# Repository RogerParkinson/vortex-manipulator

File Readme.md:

Vortex Manipulator
=

Mostly inspired by the wrist device worn by Captain Jack Harkness in _Dr Who_ and _Torchwood_, hence the name. However the design wandered somewhat from that initial idea so the look is a bit different. This is the idea I started with:

Mine is a little different, I needed more space to do what I want, so it is a bit fatter and it doesn't actually manipulate a time vortex (whatever that is). Instead it has the following functions:

 * Touch screen interface
 * Clock with optional beep and LED flash once a second, plus a function to set the time. It doesn't adjust automatically for daylight savings etc, but there is a UI to set the time manually.
 * Compass
 * Graphics demo
 * Dalek detector
 * Picture gallery (displays pictures from the SD card)
 * Heart rate monitor, including display graph and data log to SD card.
 * Sleep (power save) function, wakes up when the power button is pressed.
 * Notifications board. Messages from a Bluetooth device (eg a phone) display here.

[Lots more details here](https://github.com/RogerParkinson/vortex-manipulator)

Hardware consists of a Teensy 3.2 mounted on a custom board [the Main Board](eagle/MainBoard/Readme.md) which contains circuitry for charging the attached LiPo battery when the USB port is connected, and an LSM303 to provide compass and accelerometer functions.

A second [ILI9341 custom connector board](eagle/ILI9341-Touch-connector/Readme.md) connects to an ILI9341 touch screen. This board has a touch controller and a connector strip that matches the strip on the side of the main board.

There are some configuration settings stored on the SD card (file is hconfig.txt) which consists of the time zone, low pulse and high pulse rates. The pulse rates are used by the HRM to sound alarms if the pulse is outside that range. The time zone is used for the clock (except it isn't actually used now). The other files on the SD card are bmp files used for the picture gallery. These must be 240x320 images. All of these files are in the SDBackup directory.

Perhaps more importantly it is a development _platform_. There is plenty of spare capacity in the Teensy and there is still plenty of room in the assembly to add more stuff. The Main Board has connectors to unused pins on the Teensy as well. An example of adding more stuff is the heart rate monitor. I got hold of a better one which uses an I2C interface and, hardware-wise, it was simple to add the extra connections to the SDA and SCL for it, then a bit more programming and the job was done.

The assembly is a mix of leather and a 3D printed frame.

Parts
-

 * [Teensy 3.2](https://www.pjrc.com/store/teensy32.html) microprocessor board
 * [LSM303](http://nz.element14.com/stmicroelectronics/lsm303dlhc/sensor-3-ch-accel-mag-mod-14lga/dp/2068595) Compass/accelerometer IC *
 * [SD Card Reader](https://www.aliexpress.com/item/Free-Shipping-5PCS-67840-8001-Conn-SD-Card-HDR-9-POS-Solder-RA-SMD-Embossed-T/32651979617.html?spm=2114.01010208.3.8.SHXu2I&ws_ab_test=searchweb0_0,searchweb201602_3_10152_10065_10151_10068_436_10136_10157_10137_10060_10138_10155_10062_10156_10154_10056_10055_10054_10059_100032_100033_100031_10099_10103_10102_10096_10147_10052_10053_10050_10107_10142_10051_10084_10083_10080_10082_10081_10110_10175_10111_10112_10113_10114_10181_10037_10183_10182_10185_10033_10032_10078_10079_10077_10073_10070_10123,searchweb201603_2,ppcSwitch_4&btsid=7b9c1a86-e8c1-4082-b529-14cabbf02189&algo_expid=712bfc6c-3058-4115-9f9d-6d221787d2ec-1&algo_pvid=712bfc6c-3058-4115-9f9d-6d221787d2ec) *
 * [Lipo Battery 3.7v](https://www.aliexpress.com/item/3-7V-1000mah-753050-Lithium-Polymer-LiPo-Rechargeable-Battery-For-Mp3-MP4-MP5-DVD-PAD-mobile/32293277274.html?spm=2114.01010208.3.15.W3GGuF&ws_ab_test=searchweb0_0,searchweb201602_3_10152_10065_10151_10068_436_10136_10157_10137_10060_10138_10155_10062_10156_10154_10056_10055_10054_10059_100032_100033_100031_10099_10103_10102_10096_10147_10052_10053_10050_10107_10142_10051_10084_10083_10080_10082_10081_10110_10175_10111_10112_10113_10114_10181_10037_10183_10182_10185_10032_10078_10079_10077_10073_10070_10123,searchweb201603_2,ppcSwitch_4&btsid=7691371f-396d-424d-b6fc-32f0ece90527&algo_expid=46b76ba9-9c3b-4e16-846a-75c4c1e89c21-4&algo_pvid=46b76ba9-9c3b-4e16-846a-75c4c1e89c21)
 * [2.4" 240x320 SPI Serial TFT Color LCD Display Module+ILI9341 Touch Panel Screen](https://www.aliexpress.com/item/2-8-2-8-Inch-240x320-SPI-Serial-TFT-Color-LCD-Display-Module-Touch-Panel-Screen/32681743271.html?spm=2114.13010308.0.0.0kiaBY) Make sure you get a *touch* screen, there are screens in the same format/packing that just display with no touch.
 * [XPT2046 Touch Controller](https://www.aliexpress.com/item/Free-shipping-20pcs-lot-XPT2046-2046-TSSOP16-new-original/32639677099.html?spm=2114.13010608.0.0.BkDnSR) *
 * [MCP73811](https://www.aliexpress.com/item/100-new-origina-MCP73811T-420I-OT-battery-management-chip-73811-MCP73811-Free-shipping-best-match/32713220952.html?spm=2114.search0104.3.1.75a67645xuhfYb&ws_ab_test=searchweb0_0,searchweb201602_3_10065_10068_10547_319_317_10548_10696_10084_453_10924_10083_454_10925_10926_10618_10920_10921_10307_10922_537_536_5733313_5733211_10059_10884_5733113_10887_100031_321_5733413_322_10103_5733612_5733513,searchweb201603_2,ppcSwitch_0&algo_expid=36e5927f-8c98-4996-90c5-7ffab6aace2d-0&algo_pvid=36e5927f-8c98-4996-90c5-7ffab6aace2d) battery management chip *
 * [LP298X](http://www.datasheetcafe.com/lp298xs-datasheet-low-dropout-regulator/) voltage regulator *
 * [Speaker 8 ohm](https://www.aliexpress.com/item/Manufacturers-direct-sales-round-8-European-1W-speaker-1w8-European-speakers-8-European-1W-speaker-20mm/32777445698.html?spm=2114.10010108.1000014.5.zq1wAZ&traffic_analysisId=recommend_3035_null_null_null&scm=1007.13338.79672.000000000000000&pvid=fb37bd47-3760-417f-b739-e97fcb0411c1&tpp=1)
 * 2 LEDs (blue and green, or whatever colour you prefer)
 * 32.768Khz Crystal [soldered to the under side of the Teensy](https://www.pjrc.com/teensy/td_libs_Time.html) and a Coin Cell battery (CR2032) and holder.
 * [Switch](https://www.aliexpress.com/item/MINI-micro-Slide-Switch-On-OFF-2-Position-1P2T-SPDT-Miniature-Horizontal-Slide-Switch-SMD-7/32655484942.html?spm=2114.01010208.3.1.kFgw4d&ws_ab_test=searchweb0_0,searchweb201602_3_10152_10065_10151_10068_436_10136_10157_10137_10060_10138_10155_10062_10156_10154_10056_10055_10054_10059_100032_100033_100031_10099_10103_10102_10096_10147_10052_10053_10050_10107_10142_10051_10084_10083_10080_10082_10081_10110_10175_10111_10112_10113_10114_10181_10037_10183_10182_10185_10032_10078_10079_10077_10073_10070_10123,searchweb201603_2,ppcSwitch_4&btsid=4943b00a-2810-4553-922c-abebd41b5fcd&algo_expid=9ef925ce-c813-4853-b9b8-157b1cc2ff52-0&algo_pvid=9ef925ce-c813-4853-b9b8-157b1cc2ff52) *
 * [Button](https://www.aliexpress.com/item/Promotion-Amico-100-Pcs-6x6x4-5mm-Panel-PCB-Momentary-Tactile-Tact-Push-Button-Switch-4-Pin/32563399489.html?spm=2114.10010108.1000014.1.VHE2ua&traffic_analysisId=recommend_3035_null_null_null&scm=1007.13338.79672.000000000000000&pvid=3f217487-ecad-45bd-a56f-eb5fef49d540&tpp=1)
 * Various caps and resistors (see circuit diagrams for the boards)
 * [Heart Rate Monitor](https://www.aliexpress.com/item/Low-Power-MAX30102-Heart-Rate-Oxygen-Pulse-Breakout-for-Arduino-Replace-MAx30100/32892216359.html?spm=a2g0s.9042311.0.0.27424c4dQnQZ6O) MAX30102 based breakout board.
 
Those marked with * are all surface mounted (SMD) parts.
 
Making the Icons
-

I developed an interesting technique for generating the icons for this project and I put it in its own [project](https://github.com/RogerParkinson/MakeIcons).

The SD card
-

The project uses an SD Card and you'll find a copy of mine in the SDBackup directory. It includes some bmp files which are images displayed by the gallery app, a configuration file calle hconfig.txt and a log file called datalog.txt.

The configuration file is one line: 12,120,150,
the 12 was once a timezone but I no longer use that. 120 and 150 are heart rate limits. The display turns green when you pass 120 and red when you pass 150. For me green means I'm in a good exercise zone, but your numbers may be different.

You can add your own bmp files. As long as they are 240x320 BMP format they will display in the gallery. When I export mine from Gimp I use these settings:

Finally the datalog.txt file is a log of heart rates. The first column is a timestamp, then the beats per minute and finally the last interval between beats. It logs this every 10 minutes, the time is set in the setup() method in VortexManipulator.cpp:

```
intervals.create(10*60*1000L,new HRLogAction()); // 10 minutes
```

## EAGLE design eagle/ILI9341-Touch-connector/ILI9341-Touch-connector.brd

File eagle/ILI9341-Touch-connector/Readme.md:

ILI9341 connector for 14 pads + 4 pads for touch, broken out to 14 connector pins using a touch controller.

It is a clone of the PCB for [this screen](https://www.aliexpress.com/item/J34-F85-Free-Shipping-240x320-2-8-SPI-TFT-LCD-Touch-Panel-Serial-Port-Module-with/32599693865.html)
but without the SD card and the PCB is much smaller making it useful when you have very little room to mount it. The screen itself is available separately [here](https://www.aliexpress.com/item/J34-Free-Shipping-240x320-2-8-SPI-Serial-ILI9341-TFT-Color-LCD-Screen-Display-with-Touch/32435870215.html)

To build this you need a couple of resistors and ceramic capacitors as well as an [RT9169](https://www.aliexpress.com/item/Free-shipping-10pcs-lot-RT9169-30GV-RT9169-BK-SOT-23-new-original/32510597351.html)
and a [XPT2046 touch controller](https://www.aliexpress.com/item/Free-shipping-20pcs-lot-XPT2046-2046-TSSOP16-new-original/32639677099.html).

Aliexpress links come and go so if the links don't work then you can search for RT9169, and also for an ILI9341 screen. You want the screen _without_ the PCB because the already mounted on a PCB are too big (though they are easier to solder). Also make sure you order one with a touch capability. There are lots around that just display but are not touch screens. You also need the XPT2046 touch controller.

I used solder paste etc for the smd parts but I hand soldered the screen. It is fiddly work but I don't think it is a good idea to put the screen through an oven or hot plate.

Be careful when soldering the screen to the board. Those connections are very fine and, when soldered, rather fragile. Make sure you stick the board and screen together somehow, such as double sided tape, to prevent strain on the connection. It is important to get the screen connection around the right way. Check carefully before you solder.

For details on connecting the resulting board to your processor see [PJRC's instructions](https://www.pjrc.com/store/display_ili9341_touch.html).

<a href="https://oshpark.com/shared_projects/iFrrmh3h"></img></a>

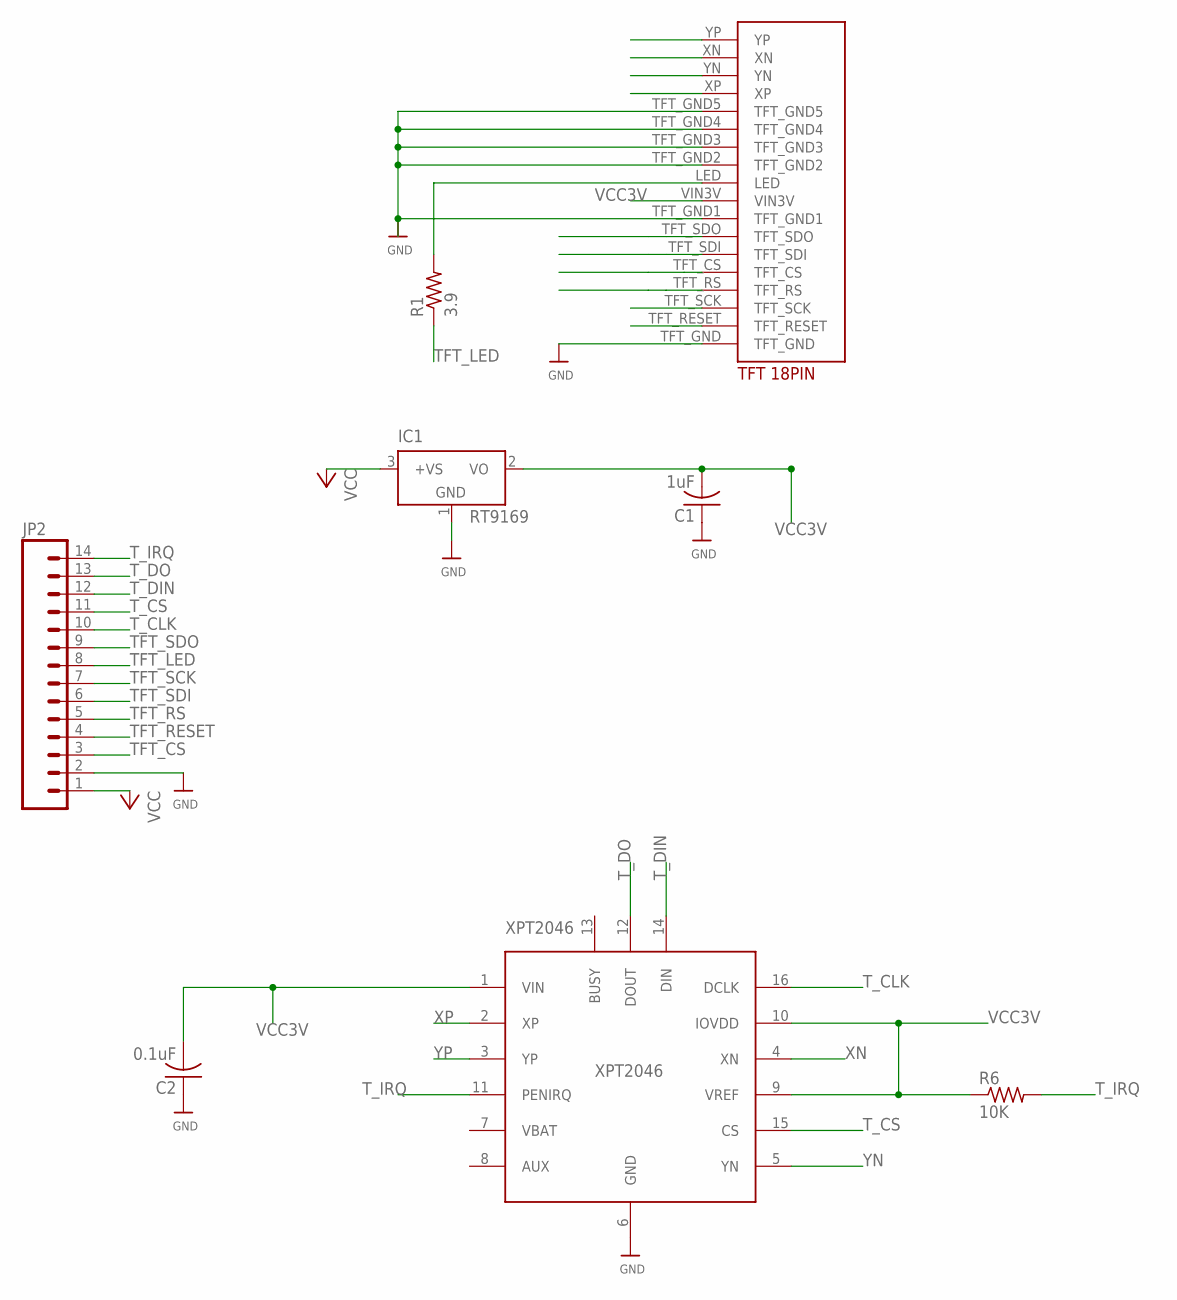
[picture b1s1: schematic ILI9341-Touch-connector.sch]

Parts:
C1: 1uF; C0805K
C2: 0.1uF; C0805K
IC1: RT9169; SOT23
JP2: M14; 1X14
R1: 3.9; R0805
R6: 10K; R0805
U$4: TFT_18PIN
XPT2046: XPT2046; TSSOP16-EXPOSED_PAD_MINIMAL

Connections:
GND: C1.1, C2.1, IC1.1 (GND), JP2.2, U$4.TFT_GND, U$4.TFT_GND1, U$4.TFT_GND2, U$4.TFT_GND3, U$4.TFT_GND4, U$4.TFT_GND5, XPT2046.6 (GND)
unnamed: R1.2, U$4.LED
TFT_CS: JP2.3, U$4.TFT_CS
TFT_LED: JP2.8, R1.1
TFT_RESET: JP2.4, U$4.TFT_RESET
TFT_RS: JP2.5, U$4.TFT_RS
TFT_SCK: JP2.7, U$4.TFT_SCK
TFT_SDI: JP2.6, U$4.TFT_SDI
TFT_SDO: JP2.9, U$4.TFT_SDO
T_CLK: JP2.10, XPT2046.16 (DCLK)
T_CS: JP2.11, XPT2046.15 (CS)
T_DIN: JP2.12, XPT2046.14 (DIN)
T_DO: JP2.13, XPT2046.12 (DOUT)
T_IRQ: JP2.14, R6.2, XPT2046.11 (PENIRQ)
VCC: IC1.3 (+VS), JP2.1
VCC3V: C1.2, C2.2, IC1.2 (VO), R6.1, U$4.VIN3V, XPT2046.1 (VIN), XPT2046.9 (VREF), XPT2046.10 (IOVDD)
XN: U$4.XN, XPT2046.4 (XN)
XP: U$4.XP, XPT2046.2 (XP)
YN: U$4.YN, XPT2046.5 (YN)
YP: U$4.YP, XPT2046.3 (YP)

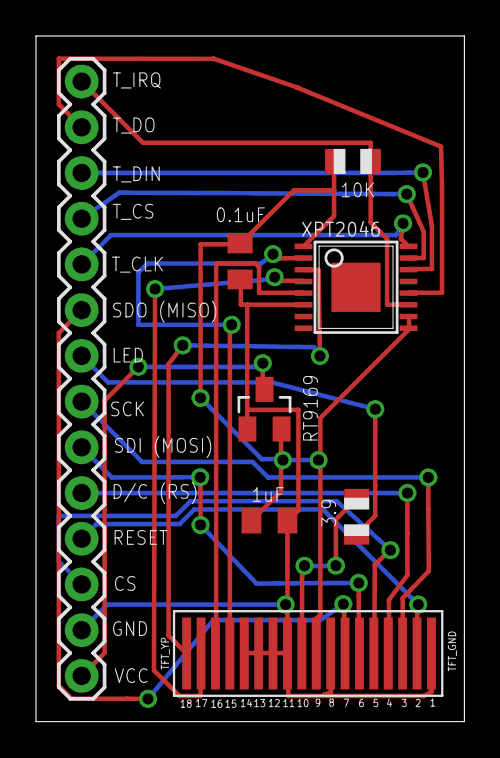
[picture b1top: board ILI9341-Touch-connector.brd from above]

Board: 2 copper layers, 23.8 x 38.1 mm, 8 parts (0 on the bottom side), 20 nets.

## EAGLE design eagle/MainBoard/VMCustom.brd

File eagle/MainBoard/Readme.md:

Main board for the Vortex Manipulator
==

Main components:

 * Teensy 3.2 board. This holds the processor and the USB connector. It also has an on board clock powered by the small battery.
 * MicroSD. This holds configuration files and images. Heart rate logs go here.
 * LSM303 which provides a compass and an accelerometer.
 * LIPO charger circuit which charges the LIPO battery when the USB is connected.
 * Through hole connectors for the ILI9841 touch screen and various other connectors.
 
In addition to the ILI9341 connector strip on the main board there is a second strip just above it which has the following:

 * GND
 * Wake pulling this low (by the pushbutton) wakes us from shutdown mode.
 * Tone connects to the speaker.
 * LED1 connects to one of the LEDs.
 * LED2 connects to one of the LEDs.
 * Pulse no longer used.
 * Power no longer used.
 * Rx not yet used but connects to the Rx of the Teensy.
 * Tx not yet used but connects to the Tx of the Teensy.
 
A third strip just in front of the Teensy has some connectors that expose the under side connections of the Teensy for future expansion. These are:

 * A13
 * 33
 * 32
 * 31
 * 30
 * 29
 * A12

The [MAX30102 heart rate monitor](https://www.aliexpress.com/item/Low-Power-MAX30102-Heart-Rate-Oxygen-Pulse-Breakout-for-Arduino-Replace-MAx30100/32892216359.html?spm=a2g0s.9042311.0.0.27424c4dVejVpp) is connected directly to the Teensy SDA and SCL pins, plus 3.3v power and GND.

Finally the Teensy on-board clock needs a backup coin cell battery connected to the battery and GND connectors on the Teensy.
 
<a href="https://oshpark.com/shared_projects/zJDmyNc4"></img></a>

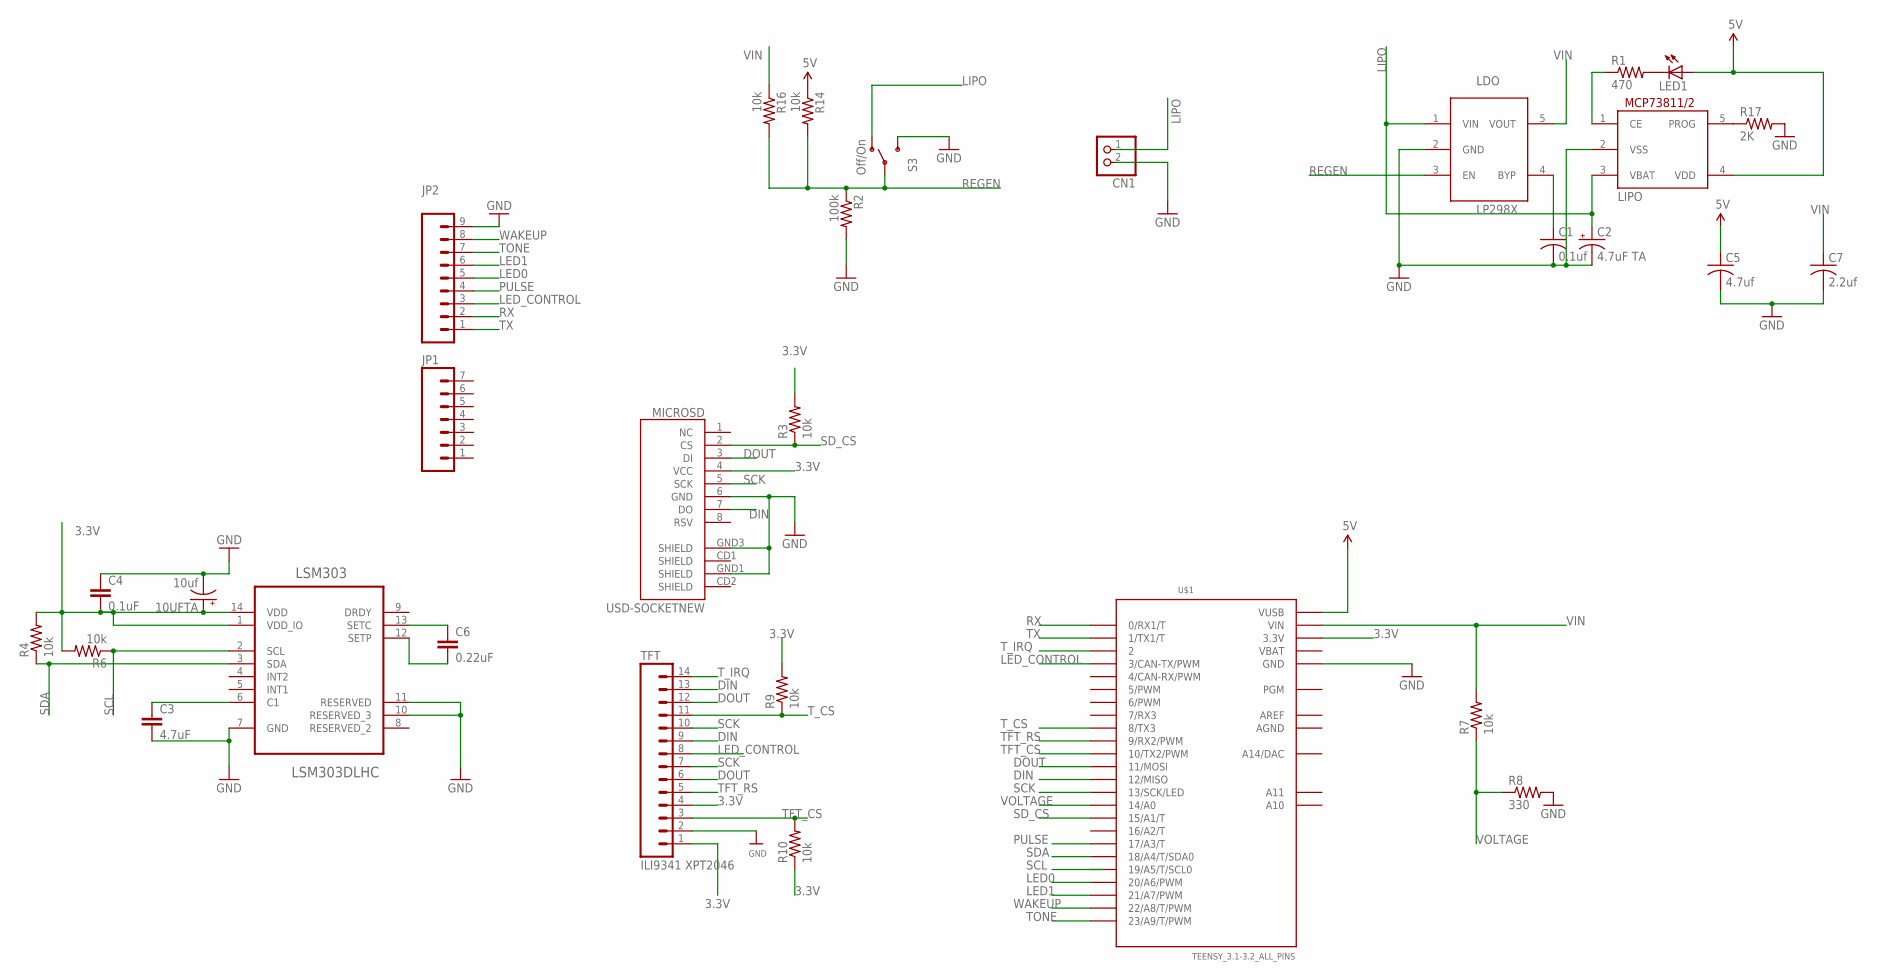
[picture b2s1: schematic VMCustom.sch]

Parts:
10UFTA: 10uf; EIA6032
C1: 0.1uf; C0805K
C2: 4.7uF TA; EIA3216
C3: 4.7uF; 0805
C4: 0.1uF; 0805
C5: 4.7uf; C0805K
C6: 0.22uF; 0805
C7: 2.2uf; C0805K
CN1: JST_2PIN-THM; JST-PH-2-THM
JP1: M07; 1X07
JP2: M09NO_SILK; 1X09_NO_SILK
LDO: LP298XS; SOT23-5L
LED1: LEDCHIPLED_0805; CHIPLED_0805
LIPO: MCP73811/2; SOT23-5L
LSM303: LSM303DLHC; LGA14R80P1X6
MICROSD: USD-SOCKETNEW; MICRO-SD-SOCKET-PP
R1: 470; M0805
R2: 100k; R0805
R3, R4, R6, R7, R9, R10: 10k; 0805
R8: 330; 0805
R14, R16: 10k; R0805
R17: 2K; M0805
S3: Off/On; SWITCH-SPST-SMD-A
TFT: ILI9341 XPT2046; 1X14
U$1: TEENSY_3.1-3.2_ALL_PINS; TEENSY_3.0-3.2&LC_ALL_PINS

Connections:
3.3V: 10UFTA.P$1 (+), C4.2, LSM303.1 (VDD_IO), LSM303.14 (VDD), MICROSD.4 (VCC), R3.2, R4.2, R6.2, R9.2, R10.1, TFT.1, TFT.4, U$1.3.3V, U$1.3.3V1 (3.3V)
5V: C5.1, LED1.A, LIPO.4 (VDD), R14.1, U$1.VUSB
AGND: U$1.AGND
AREF: U$1.AREF
DIN: MICROSD.7 (DO), TFT.9, TFT.13, U$1.12 (12/MISO)
DOUT: MICROSD.3 (DI), TFT.6, TFT.12, U$1.11 (11/MOSI)
GND: 10UFTA.P$2 (-), C1.2, C2.C (-), C3.2, C4.1, C5.2, C7.2, CN1.2 (1), JP2.9, LDO.2 (GND), LIPO.2 (VSS), LSM303.7 (GND), LSM303.10 (RESERVED_3), LSM303.11 (RESERVED), MICROSD.6 (GND), MICROSD.GND1 (SHIELD), MICROSD.GND3 (SHIELD), R2.2, R8.2, R17.2, S3.3 (S), TFT.2, U$1.GND, U$1.GND1 (GND)
LED0: JP2.5, U$1.20/A6 (20/A6/PWM)
LED1: JP2.6, U$1.21/A7 (21/A7/PWM)
LED_CONTROL: JP2.3, TFT.8, U$1.3 (3/CAN-TX/PWM)
LIPO: C2.A (+), CN1.1 (2), LDO.1 (VIN), LIPO.3 (VBAT), S3.1 (O)
unnamed: LIPO.1 (CE), R1.1
unnamed: C3.1, LSM303.6 (C1)
unnamed: LED1.C, R1.2
unnamed: C1.1, LDO.4 (BYP)
unnamed: C6.1, LSM303.13 (SETC)
unnamed: C6.2, LSM303.12 (SETP)
unnamed: LIPO.5 (PROG), R17.1
PULSE: JP2.4, U$1.17/A3 (17/A3/T)
REGEN: LDO.3 (EN), R2.1, R14.2, R16.2, S3.2
RX: JP2.2, U$1.0 (0/RX1/T)
SCK: MICROSD.5 (SCK), TFT.7, TFT.10, U$1.13 (13/SCK/LED)
SCL: LSM303.2 (SCL), R6.1, U$1.19/A5 (19/A5/T/SCL0)
SDA: LSM303.3 (SDA), R4.1, U$1.18/A4 (18/A4/T/SDA0)
SD_CS: MICROSD.2 (CS), R3.1, U$1.15/A1 (15/A1/T)
TFT_CS: R10.2, TFT.3, U$1.10 (10/TX2/PWM)
TFT_RS: TFT.5, U$1.9 (9/RX2/PWM)
TONE: JP2.7, U$1.23/A9 (23/A9/T/PWM)
TX: JP2.1, U$1.1 (1/TX1/T)
T_CS: R9.1, TFT.11, U$1.8 (8/TX3)
T_IRQ: TFT.14, U$1.2
VBAT: U$1.VBAT
VIN: C7.1, LDO.5 (VOUT), R7.2, R16.1, U$1.VIN
VOLTAGE: R7.1, R8.1, U$1.14/A0
WAKEUP: JP2.8, U$1.22/A8 (22/A8/T/PWM)

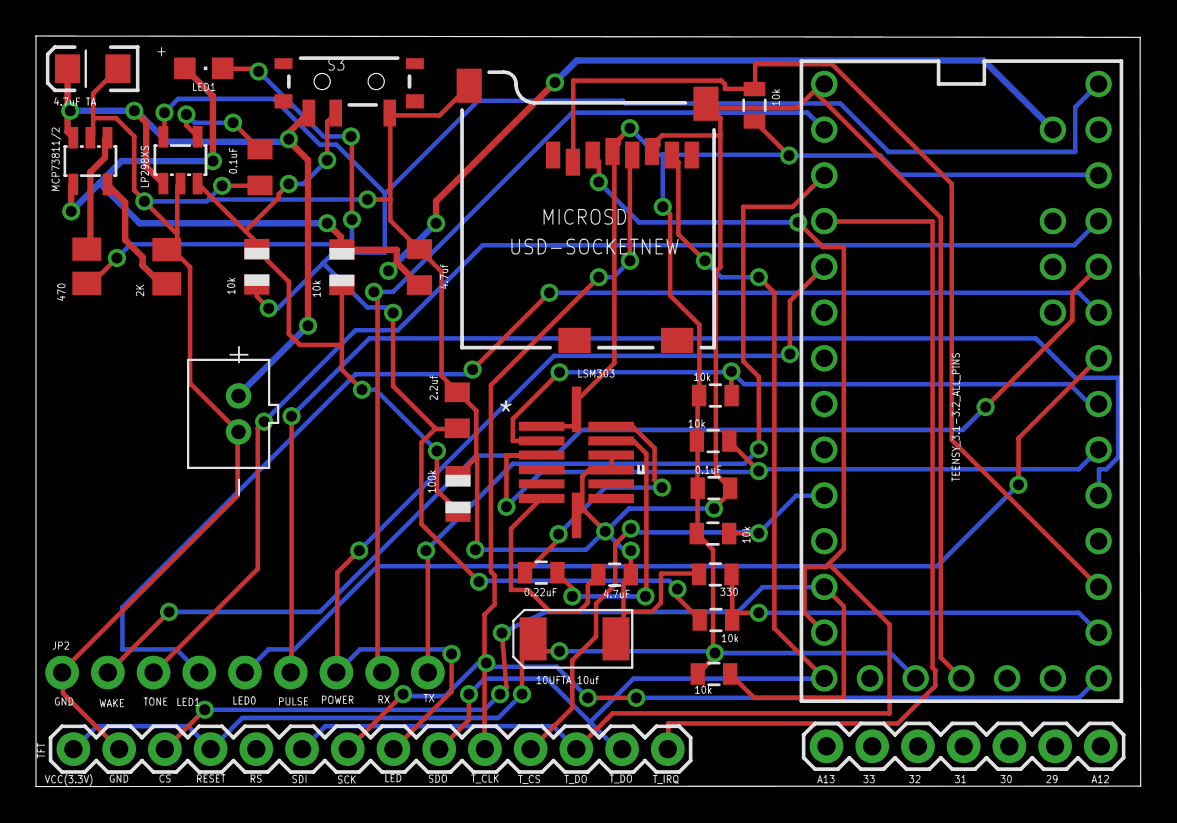
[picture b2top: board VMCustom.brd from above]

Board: 2 copper layers, 61.4 x 41.7 mm, 31 parts (0 on the bottom side), 32 nets.

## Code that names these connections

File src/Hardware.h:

/*
 * Hardware.h
 *
 *  Created on: 22/05/2013
 *      Author: roger
 */

#ifndef HARDWARE_H_
#define HARDWARE_H_
#include <LSM303.h>
#include <ILI9341_t3.h>
#include <font_Arial.h> // from ILI9341_t3
#include <XPT2046_Touchscreen.h>
#include <SD.h>
#include <Wire.h>
#include <Time.h>
#include <LowPower_Teensy3.h>
#include "heartrate/HeartRateInterrupt.h"
#include <MAX30105.h>

#include <heartRate.h>
#include "ui/Startup.h"
#include <SoftwareSerial.h>
#include <Logger.h>
#include <Timezone.h>   // https://github.com/JChristensen/Timezone
#include <TimeLib.h>    // https://github.com/PaulStoffregen/Time

//#define HARDWARE_DEBUG
#define ICON_DEBUG
#define TS_CS 8
#define TIRQ_PIN  2
#define TFT_DC  9
#define TFT_CS 10
#define SD_CS 15
extern ILI9341_t3 Graphics;

// Assign human-readable names to some common 16-bit color values:
#define	BLACK   0x0000
#define	BLUE    0x001F
#define	RED     0xF800
#define	GREEN   0x07E0
#define CYAN    0x07FF
#define MAGENTA 0xF81F
#define YELLOW  0xFFE0
#define WHITE   0xFFFF

#define TS_MINX 150
#define TS_MINY 130
#define TS_MAXX 3800
#define TS_MAXY 4000

#define TONE_PIN 23
#define LED0_PIN 20
#define LED1_PIN 21
#define VOLTAGE 0 // actually A0. This is the battery voltage measure pin 14
#define PULSE_PIN 17 // pin 17 (A3)
#define LED_CONTROL_PIN 3 // controls the LED brightness & power to compass and HRM

#define HEADER_PIXEL(data,pixel) {\
pixel[0] = (((data[0] - 33) << 2) | ((data[1] - 33) >> 4)); \
pixel[1] = ((((data[1] - 33) & 0xF) << 4) | ((data[2] - 33) >> 2)); \
pixel[2] = ((((data[2] - 33) & 0x3) << 6) | ((data[3] - 33))); \
data += 4; \
}
#define bluetooth Serial1
#define DSTRING_SIZE 60

class Icon {
public:
	unsigned int size;
	const uint16_t *icon;
	bool reversed;
	Icon(const unsigned int s, const uint16_t data[]) {
		size = s;
		icon = data;
		reversed=false;
	};
	void reverse(bool r) {
		reversed = r;
	}
	virtual ~Icon() {
	};
	const void draw(const int x, const int y) {
		if (icon != NULL) {
			int count = 0;
			for (unsigned int j = 0; j < size; j++) {

				for (unsigned int i = 0; i < size; i++) {
					uint16_t pixel = icon[count++];
					if (reversed) {
						pixel = ~pixel;
					}
					Graphics.drawPixel(x + i, y + j, pixel);
				}
			}
		}
	}
};


class Hardware_ {
private:
	Logger *loggerHardware;
	LSM303 m_lsm303;
	char dstring[DSTRING_SIZE];
	bool m_sdOK=false;
	TEENSY3_LP m_lowPower;
	int m_compassCorrection;
	bool sleeping = false;

public:
	Hardware_();
	void init();
	void shutdown();
	void sleep();
	void wake();
	bool isSleeping();
	int compassHeading();
	void compass(bool start);
	void blink0() {
		digitalWrite(LED0_PIN, HIGH);
		delay(50);
		digitalWrite(LED0_PIN, LOW);
	}
	void blink1() {
		digitalWrite(LED1_PIN, HIGH);
		delay(50);
		digitalWrite(LED1_PIN, LOW);
	}
	LSM303::vector<int16_t> getAccelerometerValues();
	bool isSDOK() { return m_sdOK;};
	bool beginSD();
	const char *timeString(long adjustedDate);
	const char *timeString(int hour, int minute, int second);
	const char *dateString(long adjustedDate);
	void setCompassCorrection(const char *str);
	int getCompassCorrection();
	void progmemPrint(const char *str);
	void progmemPrintln(const char *str);
	void printDirectory(File dir, int numTabs);
	int readInt(File dataFile);
	float getBatteryVoltage();
	void playTone(uint16_t frequency, uint32_t duration = 0, uint32_t delay_after = 40);
	void siren();
	const ILI9341_t3_font_t &getDefaultFont() {
		return Arial_10;
	}
	void dumpSD(const char *message) {
		Serial.print(PSTR("dumpSD "));
		Serial.println(message);
		File root = SD.open("/");
		printDirectory(root, 0);
		root.close();
		Serial.print(PSTR("dumpSD done ("));
		Serial.print(message);
		Serial.println(")");
	}
	uint16_t read16(File f);
	uint32_t read32(File f);
	void bufferAccelerometer();
	const char *readBluetooth();
	virtual ~Hardware_();
};

extern Hardware_ Hardware;
extern XPT2046_Touchscreen Touchscreen;
extern ILI9341_t3 Graphics;
extern MAX30105 particleSensor;
extern Timezone nz;


#endif /* HARDWARE_H_ */

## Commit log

2018-11-12 added eagle files and readme
2018-11-12 added license
2018-11-12 Optional poincare plot, added readmes, turned off startup sequence
2018-11-12 code cleanup, mostly removed commented out stuff
2018-11-25 gesture wakeup implemented in interval
2018-11-25 reworked interval classes to use millis and cycle
2018-11-25 HardwareSleep implemented as Interval
2018-11-26 removed commented out code, some minor changes to execute method
2018-11-26 Mostly debug statements. This version works w touch, but had to disable gesture and HRM
2018-11-26 All working (hrm, gesture, touch)
2018-11-26 turned off debug and added nonfunctional mars button to clock
2018-11-26 added mars time
2018-11-27 Notifications via bluetooth now working
2018-11-27 coded but not working
2018-11-29 removed 9600 init from bluetooth (seems better without)
2018-12-03 Integrating new logging mechanism finished
2018-12-03 updated for revised logging api
2018-12-03 intial panels code
2018-12-03 HR is offline
2018-12-03 HR is looking good now
2018-12-03 panels and poincare working
2018-12-03 unlog HRM
2018-12-04 changed two messages from error to info in gallery
2018-12-04 removed unnecessary gallery files
2018-12-04 removed gallery subdir (no longer required)
2018-12-04 Updated readme to refer to MakeIcons
2019-01-09 added stl file, tidied readme file, set logger factory to false
2019-01-16 Changed startup flags around
2019-01-16 added Debug flags to suppress sleeps.
2019-01-19 Added video to readme
2019-01-19 added a link to madurasoftware from the readme
2019-05-04 BLE is working
2019-05-05 code cleanup
2019-05-12 commented out test switches
2020-06-18 added time set from notification
2020-08-02 notifications working, including filters
2020-08-02 timezone added (innefficiently)
2020-08-02 Timezone working (locked to NZ)
2020-08-08 Much improved Mars time function
2020-08-10 typo
2020-12-05 flags back to production and updated to 1.54
2021-01-28 settings
2021-01-29 just internal settings

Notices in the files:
eagle/ILI9341-Touch-connector/ILI9341-Touch-connector.brd:
(c) 2016
eagle/MainBoard/VMCustom.brd:
(c)2017
parts and their libraries:
SparkFun-Connectors: Licensing: Creative Commons ShareAlike 4.0 International - https://creativecommons.org/licenses/by-sa/4.0
SparkFun-Connectors: Licensing: CC v3.0 Share-Alike You are welcome to use this library for commercial purposes.
